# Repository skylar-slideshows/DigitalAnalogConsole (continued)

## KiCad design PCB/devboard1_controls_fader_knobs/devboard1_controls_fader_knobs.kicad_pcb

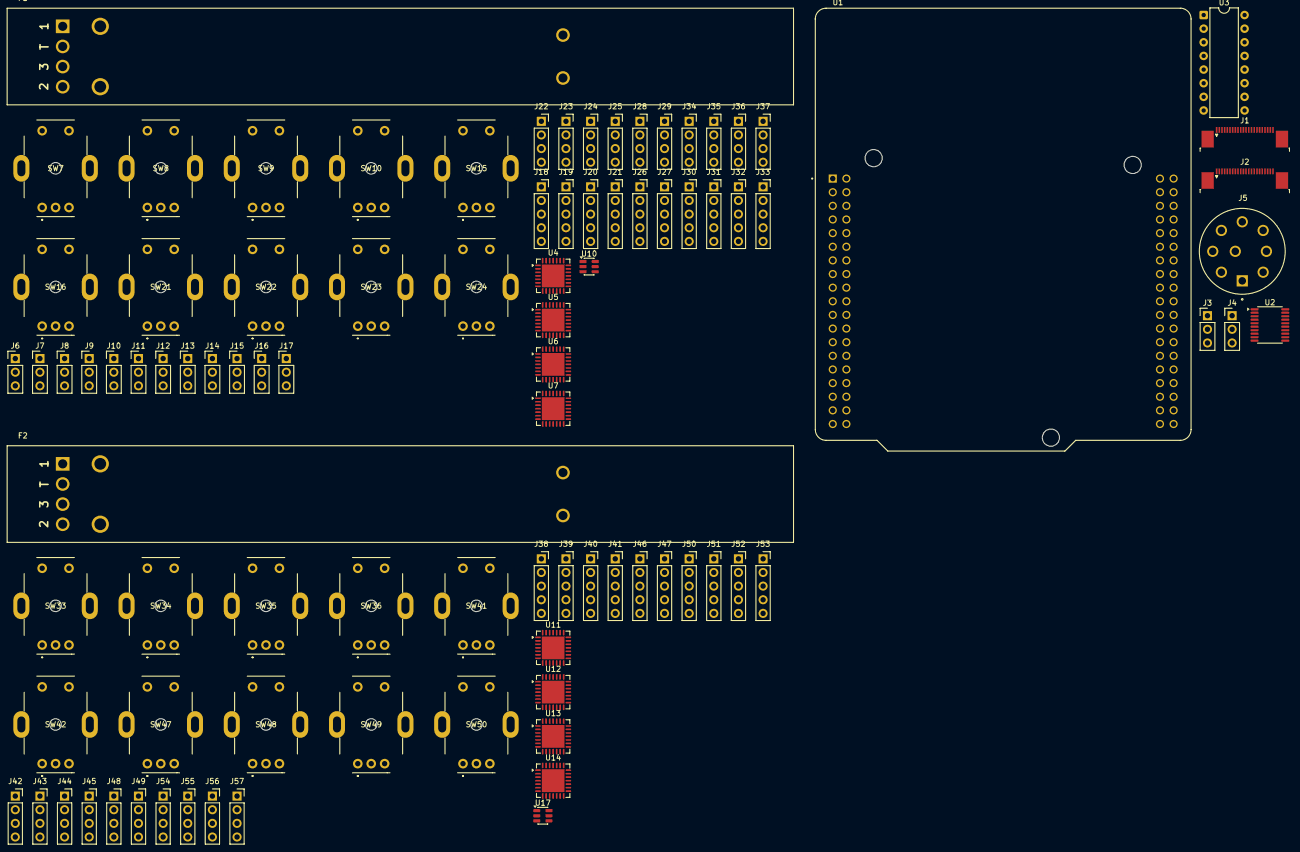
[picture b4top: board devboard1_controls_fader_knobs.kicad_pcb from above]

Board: 2 copper layers, 92 parts (0 on the bottom side), 123 nets, no tracks yet.

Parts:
F1, F2: CHNL_FADER; TRIM_RSA0N11M9A07
J1: DISP1; TE_2-1734839-2_1x22-1MP_P0.5mm_Horizontal
J2: DISP2; TE_2-1734839-2_1x22-1MP_P0.5mm_Horizontal
J3: ANLG_GND_SEL; PinHeader_1x03_P2.54mm_Vertical
J4: ANLG_REF_SEL; PinHeader_1x03_P2.54mm_Vertical
J5: POWER; CUI_SD-80BV
J6, J9, J12, J15: ADDRSEL_0; PinHeader_1x03_P2.54mm_Vertical
J7, J10, J13, J16: ADDRSEL_1; PinHeader_1x03_P2.54mm_Vertical
J8, J11, J14, J17: ADDRSEL_2; PinHeader_1x03_P2.54mm_Vertical
J18, J19, J20, J21, J26, J27, J30, J31, J32, J33, J38, J39, J40, J41, J46, J47, J50, J51, J52, J53: KNOB_LED_D1; PinSocket_1x05_P2.54mm_Vertical
J22, J23, J24, J25, J28, J29, J34, J35, J36, J37, J42, J43, J44, J45, J48, J49, J54, J55, J56, J57: KNOB_LED_P1; PinSocket_1x04_P2.54mm_Vertical
SW7, SW33: KNOB_CTRL_1A; EC11J0924411
SW8, SW34: KNOB_CTRL_2A; EC11J0924411
SW9, SW35: KNOB_CTRL_3A; EC11J0924411
SW10, SW36: KNOB_CTRL_4A; EC11J0924411
SW15, SW41: KNOB_INPUT; EC11J0924411
SW16, SW42: KNOB_PAN; EC11J0924411
SW21, SW47: KNOB_CTRL_1B; EC11J0924411
SW22, SW48: KNOB_CTRL_2B; EC11J0924411
SW23, SW49: KNOB_CTRL_3B; EC11J0924411
SW24, SW50: KNOB_CTRL_4B; EC11J0924411
U1: NUCLEO-G474RE; MODULE_NUCLEO-G474RE
U2: SN74LVC245APW; TSSOP-20_4.4x6.5mm_P0.65mm
U3: L293D; DIP-16_W7.62mm
U4, U5, U6, U7, U11, U12, U13, U14: MCP23017x-x-ML; QFN-28-1EP_6x6mm_P0.65mm_EP4.25x4.25mm
U10, U17: TTP223-BA6; SOT-23-6

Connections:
+3.3V: J6.1, J7.1, J8.1, J9.1, J10.1, J11.1, J12.1, J13.1, J14.1, J15.1, J16.1, J17.1, U4.5 (V_{DD}), U4.14 (~RESET), U5.5 (V_{DD}), U5.14 (~RESET), U6.5 (V_{DD}), U6.14 (~RESET), U7.5 (V_{DD}), U7.14 (~RESET), U10.5 (VDD), U11.5 (V_{DD}), U11.13 (A2), U11.14 (~RESET), U12.5 (V_{DD}), U12.11 (A0), U12.13 (A2), U12.14 (~RESET), U13.5 (V_{DD}), U13.12 (A1), U13.13 (A2), U13.14 (~RESET), U14.5 (V_{DD}), U14.11 (A0), U14.12 (A1), U14.13 (A2), U14.14 (~RESET), U17.5 (VDD)
+3.3VA: F1.1, F2.1, J4.2, U1.CN10_7 (AVDD)
+3V3: J4.3, J5.5, U1.CN7_5 (VDD), U1.CN7_16 (+3V3), U1.CN7_33 (VBAT)
+5V: J5.6, J22.3, J22.4, J23.3, J23.4, J24.3, J24.4, J25.3, J25.4, J28.3, J28.4, J29.3, J29.4, J34.3, J34.4, J35.3, J35.4, J36.3, J36.4, J37.3, J37.4, J42.3, J42.4, J43.3, J43.4, J44.3, J44.4, J45.3, J45.4, J48.3, J48.4, J49.3, J49.4, J54.3, J54.4, J55.3, J55.4, J56.3, J56.4, J57.3, J57.4, U1.CN7_18 (+5V), U2.1 (DIR), U2.20 (VCC), U3.1 (EN1,2), U3.9 (EN3,4), U3.16 (VCC1)
+10V: J5.7, U3.8 (VCC2)
/CHANNEL_1_CTRL/K1A: SW15.A (Pin_1), U5.19 (GPA2)
/CHANNEL_1_CTRL/K1B: SW15.B (Pin_3), U5.20 (GPA3)
/CHANNEL_1_CTRL/K1S: SW15.D (Pin_4), U5.21 (GPA4)
/CHANNEL_1_CTRL/K2A: SW7.A (Pin_1), U5.22 (GPA5)
/CHANNEL_1_CTRL/K2B: SW7.B (Pin_3), U5.23 (GPA6)
/CHANNEL_1_CTRL/K2S: SW7.D (Pin_4), U5.25 (GPB0)
/CHANNEL_1_CTRL/K3A: SW21.A (Pin_1), U5.26 (GPB1)
/CHANNEL_1_CTRL/K3B: SW21.B (Pin_3), U5.27 (GPB2)
/CHANNEL_1_CTRL/K3S: SW21.D (Pin_4), U5.28 (GPB3)
/CHANNEL_1_CTRL/K4A: SW8.A (Pin_1), U5.1 (GPB4)
/CHANNEL_1_CTRL/K4B: SW8.B (Pin_3), U5.2 (GPB5)
/CHANNEL_1_CTRL/K4S: SW8.D (Pin_4), U5.3 (GPB6)
/CHANNEL_1_CTRL/K5A: SW22.A (Pin_1), U6.17 (GPA0)
/CHANNEL_1_CTRL/K5B: SW22.B (Pin_3), U6.18 (GPA1)
/CHANNEL_1_CTRL/K5S: SW22.D (Pin_4), U6.19 (GPA2)
/CHANNEL_1_CTRL/K6A: SW9.A (Pin_1), U6.20 (GPA3)
/CHANNEL_1_CTRL/K6B: SW9.B (Pin_3), U6.21 (GPA4)
/CHANNEL_1_CTRL/K6S: SW9.D (Pin_4), U6.22 (GPA5)
/CHANNEL_1_CTRL/K7A: SW23.A (Pin_1), U6.23 (GPA6)
/CHANNEL_1_CTRL/K7B: SW23.B (Pin_3), U6.25 (GPB0)
/CHANNEL_1_CTRL/K7S: SW23.D (Pin_4), U6.26 (GPB1)
/CHANNEL_1_CTRL/K8A: SW10.A (Pin_1), U6.27 (GPB2)
/CHANNEL_1_CTRL/K8B: SW10.B (Pin_3), U6.28 (GPB3)
/CHANNEL_1_CTRL/K8S: SW10.D (Pin_4), U6.1 (GPB4)
/CHANNEL_1_CTRL/K9A: SW24.A (Pin_1), U6.2 (GPB5)
/CHANNEL_1_CTRL/K9B: SW24.B (Pin_3), U6.3 (GPB6)
/CHANNEL_1_CTRL/K9S: SW24.D (Pin_4), U7.17 (GPA0)
/CHANNEL_1_CTRL/K10A: SW16.A (Pin_1), U7.18 (GPA1)
/CHANNEL_1_CTRL/K10B: SW16.B (Pin_3), U7.19 (GPA2)
/CHANNEL_1_CTRL/K10S: SW16.D (Pin_4), U7.20 (GPA3)
/CHANNEL_2_CTRL/K1A: SW41.A (Pin_1), U12.19 (GPA2)
/CHANNEL_2_CTRL/K1B: SW41.B (Pin_3), U12.20 (GPA3)
/CHANNEL_2_CTRL/K1S: SW41.D (Pin_4), U12.21 (GPA4)
/CHANNEL_2_CTRL/K2A: SW33.A (Pin_1), U12.22 (GPA5)
/CHANNEL_2_CTRL/K2B: SW33.B (Pin_3), U12.23 (GPA6)
/CHANNEL_2_CTRL/K2S: SW33.D (Pin_4), U12.25 (GPB0)
/CHANNEL_2_CTRL/K3A: SW47.A (Pin_1), U12.26 (GPB1)
/CHANNEL_2_CTRL/K3B: SW47.B (Pin_3), U12.27 (GPB2)
/CHANNEL_2_CTRL/K3S: SW47.D (Pin_4), U12.28 (GPB3)
/CHANNEL_2_CTRL/K4A: SW34.A (Pin_1), U12.1 (GPB4)
/CHANNEL_2_CTRL/K4B: SW34.B (Pin_3), U12.2 (GPB5)
/CHANNEL_2_CTRL/K4S: SW34.D (Pin_4), U12.3 (GPB6)
/CHANNEL_2_CTRL/K5A: SW48.A (Pin_1), U13.17 (GPA0)
/CHANNEL_2_CTRL/K5B: SW48.B (Pin_3), U13.18 (GPA1)
/CHANNEL_2_CTRL/K5S: SW48.D (Pin_4), U13.19 (GPA2)
/CHANNEL_2_CTRL/K6A: SW35.A (Pin_1), U13.20 (GPA3)
/CHANNEL_2_CTRL/K6B: SW35.B (Pin_3), U13.21 (GPA4)
/CHANNEL_2_CTRL/K6S: SW35.D (Pin_4), U13.22 (GPA5)
/CHANNEL_2_CTRL/K7A: SW49.A (Pin_1), U13.23 (GPA6)
/CHANNEL_2_CTRL/K7B: SW49.B (Pin_3), U13.25 (GPB0)
/CHANNEL_2_CTRL/K7S: SW49.D (Pin_4), U13.26 (GPB1)
/CHANNEL_2_CTRL/K8A: SW36.A (Pin_1), U13.27 (GPB2)
/CHANNEL_2_CTRL/K8B: SW36.B (Pin_3), U13.28 (GPB3)
/CHANNEL_2_CTRL/K8S: SW36.D (Pin_4), U13.1 (GPB4)
/CHANNEL_2_CTRL/K9A: SW50.A (Pin_1), U13.2 (GPB5)
/CHANNEL_2_CTRL/K9B: SW50.B (Pin_3), U13.3 (GPB6)
/CHANNEL_2_CTRL/K9S: SW50.D (Pin_4), U14.17 (GPA0)
/CHANNEL_2_CTRL/K10A: SW42.A (Pin_1), U14.18 (GPA1)
/CHANNEL_2_CTRL/K10B: SW42.B (Pin_3), U14.19 (GPA2)
/CHANNEL_2_CTRL/K10S: SW42.D (Pin_4), U14.20 (GPA3)
FADER1_ADC: F1.2, U1.CN7_28 (PA0)
FADER1_MOTOR1: U1.CN7_17 (PA15), U2.2 (A1)
FADER1_MOTOR2: U1.CN10_31 (PB3), U2.3 (A2)
FADER1_TOUCH: U1.CN10_18 (PB11), U10.1 (Q)
FADER2_ADC: F2.2, U1.CN7_30 (PA1)
FADER2_MOTOR1: U1.CN10_13 (PA6), U2.8 (A7)
FADER2_MOTOR2: U1.CN7_32 (PA4), U2.9 (A8)
FADER2_TOUCH: U1.CN10_16 (PB12), U17.1 (Q)
GND: J3.3, J5.8, J6.3, J7.3, J8.3, J9.3, J10.3, J11.3, J12.3, J13.3, J14.3, J15.3, J16.3, J17.3, J22.1, J22.2, J23.1, J23.2, J24.1, J24.2, J25.1, J25.2, J28.1, J28.2, J29.1, J29.2, J34.1, J34.2, J35.1, J35.2, J36.1, J36.2, J37.1, J37.2, J42.1, J42.2, J43.1, J43.2, J44.1, J44.2, J45.1, J45.2, J48.1, J48.2, J49.1, J49.2, J54.1, J54.2, J55.1, J55.2, J56.1, J56.2, J57.1, J57.2, SW7.C (Pin_2), SW7.E (Pin_5), SW7.G (Pin_6), SW8.C (Pin_2), SW8.E (Pin_5), SW8.G (Pin_6), SW9.C (Pin_2), SW9.E (Pin_5), SW9.G (Pin_6), SW10.C (Pin_2), SW10.E (Pin_5), SW10.G (Pin_6), SW15.C (Pin_2), SW15.E (Pin_5), SW15.G (Pin_6), SW16.C (Pin_2), SW16.E (Pin_5), SW16.G (Pin_6), SW21.C (Pin_2), SW21.E (Pin_5), SW21.G (Pin_6), SW22.C (Pin_2), SW22.E (Pin_5), SW22.G (Pin_6), SW23.C (Pin_2), SW23.E (Pin_5), SW23.G (Pin_6), SW24.C (Pin_2), SW24.E (Pin_5), SW24.G (Pin_6), SW33.C (Pin_2), SW33.E (Pin_5), SW33.G (Pin_6), SW34.C (Pin_2), SW34.E (Pin_5), SW34.G (Pin_6), SW35.C (Pin_2), SW35.E (Pin_5), SW35.G (Pin_6), SW36.C (Pin_2), SW36.E (Pin_5), SW36.G (Pin_6), SW41.C (Pin_2), SW41.E (Pin_5), SW41.G (Pin_6), SW42.C (Pin_2), SW42.E (Pin_5), SW42.G (Pin_6), SW47.C (Pin_2), SW47.E (Pin_5), SW47.G (Pin_6), SW48.C (Pin_2), SW48.E (Pin_5), SW48.G (Pin_6), SW49.C (Pin_2), SW49.E (Pin_5), SW49.G (Pin_6), SW50.C (Pin_2), SW50.E (Pin_5), SW50.G (Pin_6), U1.CN7_8 (GND_CN7_8), U1.CN7_19 (GND_CN7_19), U1.CN7_20 (GND_CN7_20), U1.CN7_22 (GND_CN7_22), U1.CN10_9 (GND_CN10_9), U1.CN10_20 (GND_CN10_20), U2.4 (A3), U2.5 (A4), U2.6 (A5), U2.7 (A6), U2.10 (GND), U2.13 (B6), U2.14 (B5), U2.15 (B4), U2.16 (B3), U2.19 (~OE), U3.4 (GND), U3.5 (GND), U3.12 (GND), U3.13 (GND), U4.6 (V_{SS}), U4.29 (EP), U5.6 (V_{SS}), U5.29 (EP), U6.6 (V_{SS}), U6.29 (EP), U7.6 (V_{SS}), U7.29 (EP), U10.2 (VSS), U10.4 (AHLB), U10.6 (TOG), U11.6 (V_{SS}), U11.11 (A0), U11.12 (A1), U11.29 (EP), U12.6 (V_{SS}), U12.12 (A1), U12.29 (EP), U13.6 (V_{SS}), U13.11 (A0), U13.29 (EP), U14.6 (V_{SS}), U14.29 (EP), U17.2 (VSS), U17.4 (AHLB), U17.6 (TOG)
GNDA: F1.3, F2.3, J3.2, U1.CN10_32 (AGND)
KNOB_I2C_CL: U1.CN10_3 (PB8), U4.8 (SCK), U5.8 (SCK), U6.8 (SCK), U7.8 (SCK), U11.8 (SCK), U12.8 (SCK), U13.8 (SCK), U14.8 (SCK)
KNOB_I2C_DA: U1.CN7_21 (PB7), U4.9 (SDA), U5.9 (SDA), U6.9 (SDA), U7.9 (SDA), U11.9 (SDA), U12.9 (SDA), U13.9 (SDA), U14.9 (SDA)
LED_BRIGHT_PWM: J18.4, J19.4, J20.4, J21.4, J26.4, J27.4, J30.4, J31.4, J32.4, J33.4, J38.4, J39.4, J40.4, J41.4, J46.4, J47.4, J50.4, J51.4, J52.4, J53.4, U1.CN10_23 (PA8)
LED_CL: J18.2, J19.2, J20.2, J21.2, J26.2, J27.2, J30.2, J31.2, J32.2, J33.2, J38.2, J39.2, J40.2, J41.2, J46.2, J47.2, J50.2, J51.2, J52.2, J53.2, U1.CN7_23 (PC13)
LED_DA: J26.1, U1.CN7_35 (PC2)
LED_LATCH: J18.3, J19.3, J20.3, J21.3, J26.3, J27.3, J30.3, J31.3, J32.3, J33.3, J38.3, J39.3, J40.3, J41.3, J46.3, J47.3, J50.3, J51.3, J52.3, J53.3, U1.CN7_37 (PC3)
MOT1A_DIR: F1.A (Pin_5), U3.3 (1Y)
MOT1B_DIR: F1.B (Pin_6), U3.6 (2Y)
MOT2A_DIR: F2.A (Pin_5), U3.11 (3Y)
MOT2B_DIR: F2.B (Pin_6), U3.14 (4Y)
unnamed: F1.T (Pin_4), U10.3 (I)
unnamed: F2.T (Pin_4), U17.3 (I)
unnamed: J3.1, J5.2
unnamed: J4.1, J5.4
unnamed: J6.2, U4.11 (A0)
unnamed: J7.2, U4.12 (A1)
unnamed: J8.2, U4.13 (A2)
unnamed: J9.2, U5.11 (A0)
unnamed: J10.2, U5.12 (A1)
unnamed: J11.2, U5.13 (A2)
unnamed: J12.2, U6.11 (A0)
unnamed: J13.2, U6.12 (A1)
unnamed: J14.2, U6.13 (A2)
unnamed: J15.2, U7.11 (A0)
unnamed: J16.2, U7.12 (A1)
unnamed: J17.2, U7.13 (A2)
unnamed: J18.1, J26.5
unnamed: J18.5, J30.1
unnamed: J19.1, J30.5
unnamed: J19.5, J31.1
unnamed: J20.1, J31.5
unnamed: J20.5, J32.1
unnamed: J21.1, J32.5
unnamed: J21.5, J33.1
unnamed: J27.1, J33.5
unnamed: J38.1, J46.5
unnamed: J38.5, J50.1
unnamed: J39.1, J50.5
unnamed: J39.5, J51.1
unnamed: J40.1, J51.5
unnamed: J40.5, J52.1
unnamed: J41.1, J52.5
unnamed: J41.5, J53.1
unnamed: J47.1, J53.5
unnamed: U2.18 (B1), U3.2 (1A)
unnamed: U2.17 (B2), U3.7 (2A)
unnamed: U2.12 (B7), U3.10 (3A)
unnamed: U2.11 (B8), U3.15 (4A)

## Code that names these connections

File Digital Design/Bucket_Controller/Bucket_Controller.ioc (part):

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Mcu.Name=STM32G474R(B-C-E)Tx
Mcu.Package=LQFP64
Mcu.UserName=STM32G474RETx
PA0.GPIOParameters=GPIO_Label
PA0.GPIO_Label=FADER1_ADC
PA0.Mode=IN1-Single-Ended
PA0.Signal=ADC1_IN1
PA1.GPIOParameters=GPIO_Label
PA1.GPIO_Label=FADER2_ADC
PA1.Mode=IN2-Single-Ended
PA1.Signal=ADC1_IN2
PA11.GPIOParameters=GPIO_Label
PA11.GPIO_Label=FADER3_MOTOR1
PA11.Signal=S_TIM4_CH1
PA12.GPIOParameters=GPIO_Label
PA12.GPIO_Label=FADER3_MOTOR2
PA12.Signal=S_TIM4_CH2
PA15.GPIOParameters=GPIO_Label
PA15.GPIO_Label=FADER1_MOTOR1
PA15.Signal=S_TIM2_CH1
PA2.GPIOParameters=GPIO_Label
PA2.GPIO_Label=FADER3_ADC
PA2.Mode=IN3-Single-Ended
PA2.Signal=ADC1_IN3
PA3.GPIOParameters=GPIO_Label
PA3.GPIO_Label=FADER4_ADC
PA3.Mode=IN4-Single-Ended
PA3.Signal=ADC1_IN4
PA4.GPIOParameters=GPIO_Label
PA4.GPIO_Label=FADER2_MOTOR2
PA4.Signal=S_TIM3_CH2
PA5.GPIOParameters=GPIO_Label
PA5.GPIO_Label=CV_SPI1_CL
PA5.Mode=TX_Only_Simplex_Unidirect_Master
PA5.Signal=SPI1_SCK
PA6.GPIOParameters=GPIO_Label
PA6.GPIO_Label=FADER2_MOTOR1
PA6.Signal=S_TIM3_CH1
PA7.GPIOParameters=GPIO_Label
PA7.GPIO_Label=CV_SPI1_MOSI
PA7.Mode=TX_Only_Simplex_Unidirect_Master
PA7.Signal=SPI1_MOSI
PB11.GPIOParameters=GPIO_Label
PB11.GPIO_Label=FADER1_TOUCH
PB11.Signal=GPIO_Input
PB12.GPIOParameters=GPIO_Label
PB12.GPIO_Label=FADER2_TOUCH
PB12.Signal=GPIO_Input
PB13.GPIOParameters=GPIO_Label
PB13.GPIO_Label=FADER3_TOUCH
PB13.Signal=GPIO_Input
PB14.GPIOParameters=GPIO_Label
PB14.GPIO_Label=FADER4_TOUCH
PB14.Signal=GPIO_Input
PB15.GPIOParameters=GPIO_Label
PB15.GPIO_Label=DISP12_SPI2_MOSI
PB15.Mode=TX_Only_Simplex_Unidirect_Master
PB15.Signal=SPI2_MOSI
PB2.GPIOParameters=GPIO_Label
PB2.GPIO_Label=FADER4_MOTOR1
PB2.Signal=S_TIM5_CH1
PB3.GPIOParameters=GPIO_Label
PB3.GPIO_Label=FADER1_MOTOR2
PB3.Signal=S_TIM2_CH2
PB5.GPIOParameters=GPIO_Label
PB5.GPIO_Label=DISP34_SPI3_MOSI
PB5.Mode=TX_Only_Simplex_Unidirect_Master
PB5.Signal=SPI3_MOSI
PB7.GPIOParameters=GPIO_Label
PB7.GPIO_Label=KNOB_I2C1_DA
PB7.Mode=I2C
PB7.Signal=I2C1_SDA
PB8-BOOT0.GPIOParameters=GPIO_Label
PB8-BOOT0.GPIO_Label=KNOB_I2C1_CL
PB8-BOOT0.Mode=I2C
PB8-BOOT0.Signal=I2C1_SCL
PC0.GPIOParameters=GPIO_Label
PC0.GPIO_Label=LED_BRIGHT_PWM
PC0.Signal=S_TIM1_CH1
PC1.GPIOParameters=GPIO_Label
PC1.GPIO_Label=DISP_BRIGHT_PWM
PC1.Signal=S_TIM1_CH2
PC10.GPIOParameters=GPIO_Label
PC10.GPIO_Label=DISP34_SPI3_CL
PC10.Mode=TX_Only_Simplex_Unidirect_Master
PC10.Signal=SPI3_SCK
PC12.GPIOParameters=GPIO_Label
PC12.GPIO_Label=FADER4_MOTOR2
PC12.Signal=S_TIM5_CH2
PC13.GPIOParameters=GPIO_Label
PC13.GPIO_Label=LED_CL
PC13.Signal=GPIO_Output
PC2.GPIOParameters=GPIO_Label
PC2.GPIO_Label=LED_DA
PC2.Signal=GPIO_Output
PC3.GPIOParameters=GPIO_Label
PC3.GPIO_Label=LED_LATCH
PC3.Signal=GPIO_Output
PC4.GPIOParameters=GPIO_Label
PC4.GPIO_Label=BTNS_I2C2_CL
PC4.Mode=I2C
PC4.Signal=I2C2_SCL
PC8.GPIOParameters=GPIO_Label
PC8.GPIO_Label=MASTER_I2C3_CL
PC8.Mode=I2C
PC8.Signal=I2C3_SCL
PC9.GPIOParameters=GPIO_Label
PC9.GPIO_Label=MASTER_I2C3_DA
PC9.Mode=I2C
PC9.Signal=I2C3_SDA
PF0-OSC_IN.GPIOParameters=GPIO_Label
PF0-OSC_IN.GPIO_Label=BTNS_I2C2_DA
PF0-OSC_IN.Mode=I2C
PF0-OSC_IN.Signal=I2C2_SDA
PF1-OSC_OUT.GPIOParameters=GPIO_Label
PF1-OSC_OUT.GPIO_Label=DISP12_SPI2_CL
PF1-OSC_OUT.Mode=TX_Only_Simplex_Unidirect_Master
PF1-OSC_OUT.Signal=SPI2_SCK
RCC.HSE_VALUE=8000000
RCC.SYSCLKFreq_VALUE=170000000
RCC.SYSCLKSource=RCC_SYSCLKSOURCE_PLLCLK
board=custom
